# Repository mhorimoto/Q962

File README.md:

# Q962
ロータリーエンコーダによる距離測定にもちいるためのチャタリング防止回路

<!--stackedit_data:
eyJoaXN0b3J5IjpbLTg3MzQxODkwMF19
-->

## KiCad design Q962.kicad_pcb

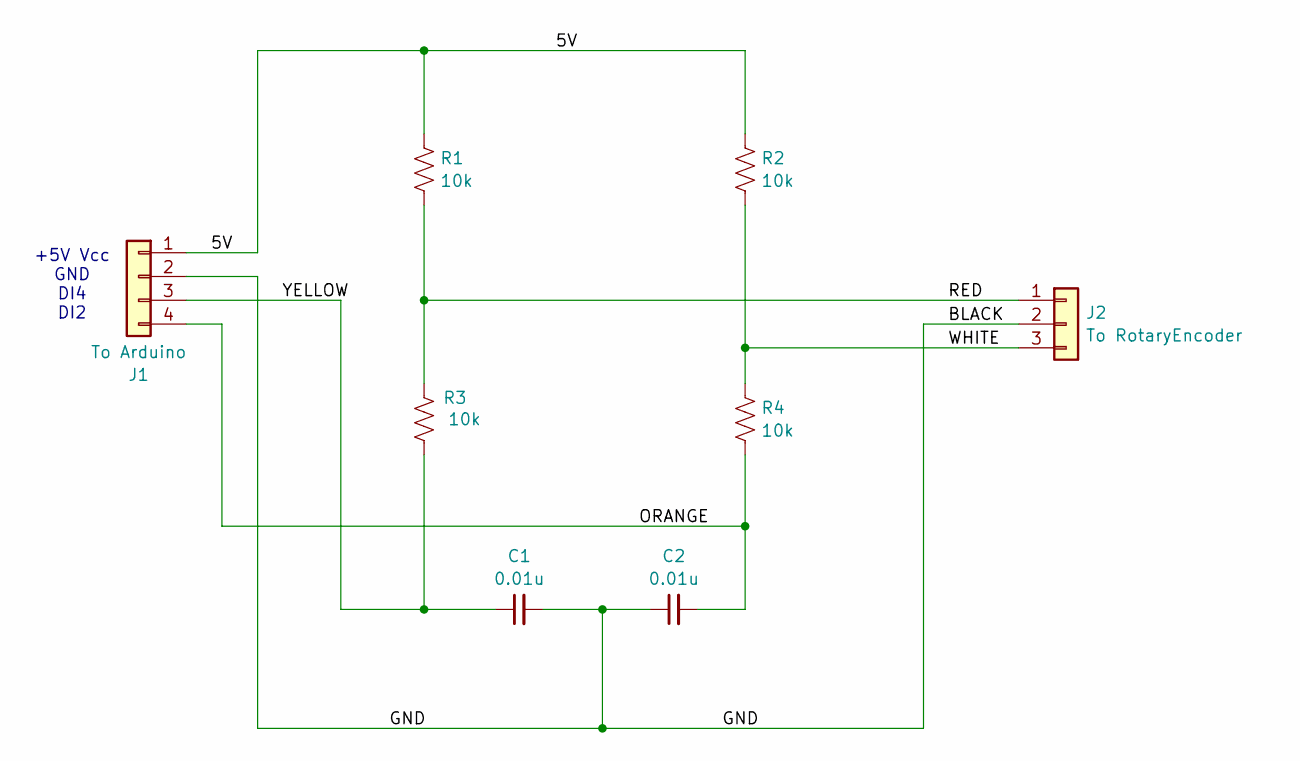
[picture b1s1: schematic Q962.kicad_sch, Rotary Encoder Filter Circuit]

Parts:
C1, C2: 0.01u; C_Disc_D3.0mm_W1.6mm_P2.50mm
J1: To Arduino; JST_XH_B4B-XH-A_1x04_P2.50mm_Vertical
J2: To RotaryEncoder; JST_XH_B3B-XH-A_1x03_P2.50mm_Vertical
R1, R2, R3, R4: 10k; R_Axial_DIN0207_L6.3mm_D2.5mm_P10.16mm_Horizontal

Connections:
/5V: J1.1, R1.1, R2.2
/BLACK: C1.2, C2.1, J1.2, J2.2
/ORANGE: C2.2, J1.4, R4.1
/RED: J2.1, R1.2, R3.2
/WHITE: J2.3, R2.1, R4.2
/YELLOW: C1.1, J1.3, R3.1

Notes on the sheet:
+5V Vcc GND DI4 DI2

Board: 2 copper layers, 8 parts (0 on the bottom side), 6 nets, no tracks yet.

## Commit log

2024-09-18 README.md updated from https://stackedit.io/
2025-08-17 KiCAD V9.0
